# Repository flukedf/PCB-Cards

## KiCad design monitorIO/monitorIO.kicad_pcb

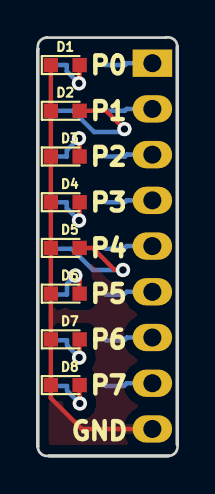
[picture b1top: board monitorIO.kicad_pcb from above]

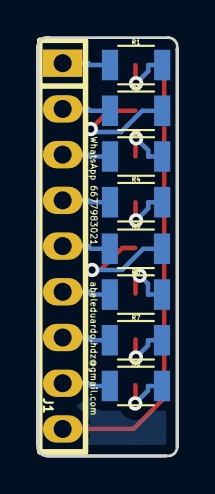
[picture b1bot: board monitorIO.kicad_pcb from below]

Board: 2 copper layers, 7.7 x 23.2 mm, 17 parts (9 on the bottom side), 17 nets.

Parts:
D1: P0; LED_0603
D2: P1; LED_0603
D3: P2; LED_0603
D4: P3; LED_0603
D5: P4; LED_0603
D6: P5; LED_0603
D7: P6; LED_0603
D8: P7; LED_0603
J1: Conn_01x09_Female; pin_strip_9
R1, R2, R3, R4, R5, R6, R7, R8: 220; R_1206

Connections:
GND: D1.1, D2.1, D3.1, D4.1, D5.1, D6.1, D7.1, D8.1, J1.9
unnamed: D1.2, R1.2
unnamed: D2.2, R2.2
unnamed: D3.2, R3.2
unnamed: D4.2, R4.2
unnamed: D5.2, R5.2
unnamed: D6.2, R6.2
unnamed: D7.2, R7.2
unnamed: D8.2, R8.2
unnamed: J1.1, R1.1
unnamed: J1.2, R2.1
unnamed: J1.3, R3.1
unnamed: J1.4, R4.1
unnamed: J1.5, R5.1
unnamed: J1.6, R6.1
unnamed: J1.7, R7.1
unnamed: J1.8, R8.1

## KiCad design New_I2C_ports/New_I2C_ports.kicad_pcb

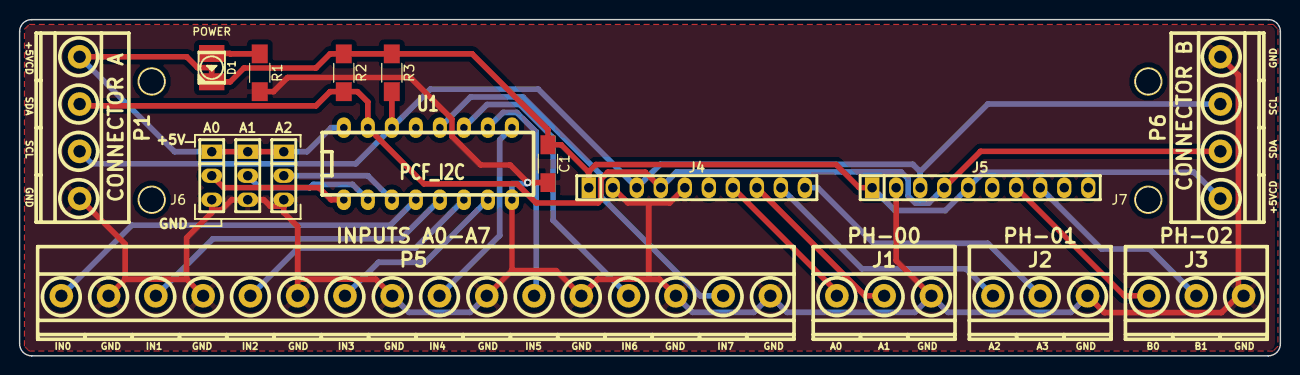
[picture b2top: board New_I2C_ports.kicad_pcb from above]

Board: 2 copper layers, 133.4 x 35.6 mm, 19 parts (0 on the bottom side), 22 nets.

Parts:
A0: A0; pin_strip_3
A1: A1; pin_strip_3
A2: A2; pin_strip_3
C1: 100nF; C_1206_HandSoldering
D1: POWER; Led_PLCC2_3528
J1: PH-00; mkds_1,5-3
J2: PH-01; mkds_1,5-3
J3: PH-02; mkds_1,5-3
J4: ADC-01; pin_strip_10
J5: ADC-02; pin_strip_10
J6: H1; Bracket_RielDin_2_hole
J7: H2; Bracket_RielDin_2_hole
P1: CONNECTOR A; mkds_1,5-4
P5: INPUTS A0-A7; mkds_1,5-16
P6: CONNECTOR B; mkds_1,5-4
R1: 330; R_1206_HandSoldering
R2, R3: 10K; R_1206_HandSoldering
U1: PCF_I2C; dil_16-300

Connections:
+5V: A0.1, A1.1, A2.1, C1.1, D1.2, J4.1, J5.1, J5.5, P1.1, P6.1, R2.1, R3.1, U1.16
A0: J1.1, J4.7
A1: J1.2, J4.8
A2: J2.1, J4.9
A3: J2.2, J4.10
B0: J3.1, J5.7
B1: J3.2, J5.8
GND: A0.3, A1.3, A2.3, C1.2, J1.3, J2.3, J3.3, J4.2, J4.5, J5.2, P1.4, P5.2, P5.4, P5.6, P5.8, P5.10, P5.12, P5.14, P5.16, P6.4, R1.2, U1.8
IN1: P5.1, U1.4
IN2: P5.3, U1.5
IN3: P5.5, U1.6
IN4: P5.7, U1.7
IN5: P5.9, U1.9
IN6: P5.11, U1.10
IN7: P5.13, U1.11
IN8: P5.15, U1.12
unnamed: D1.1, R1.1
unnamed: A0.2, U1.1
unnamed: A1.2, U1.2
unnamed: A2.2, U1.3
SCL: J4.3, J5.3, P1.3, P6.3, R3.2, U1.14
SDA: J4.4, J5.4, P1.2, P6.2, R2.2, U1.15

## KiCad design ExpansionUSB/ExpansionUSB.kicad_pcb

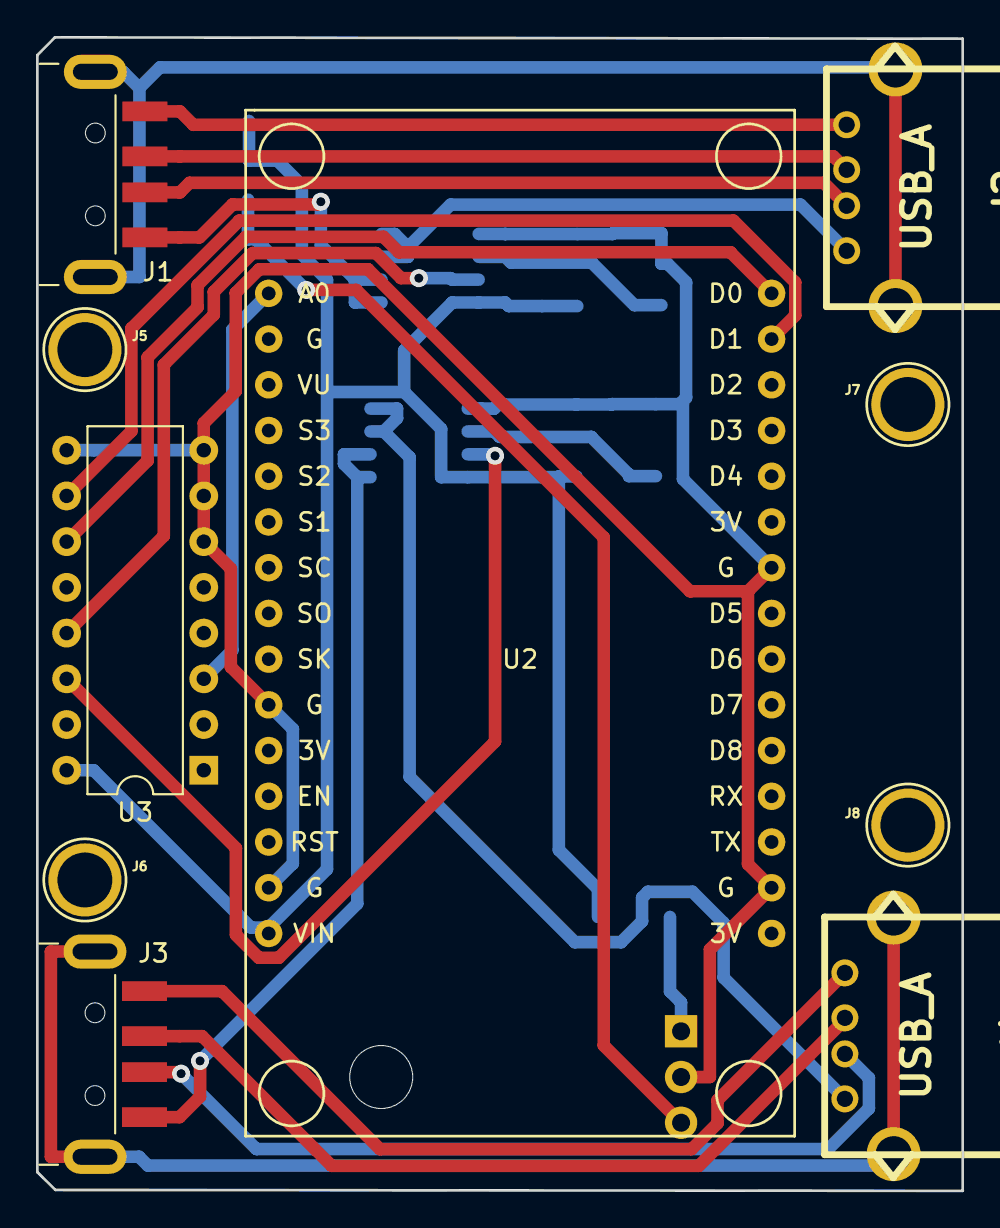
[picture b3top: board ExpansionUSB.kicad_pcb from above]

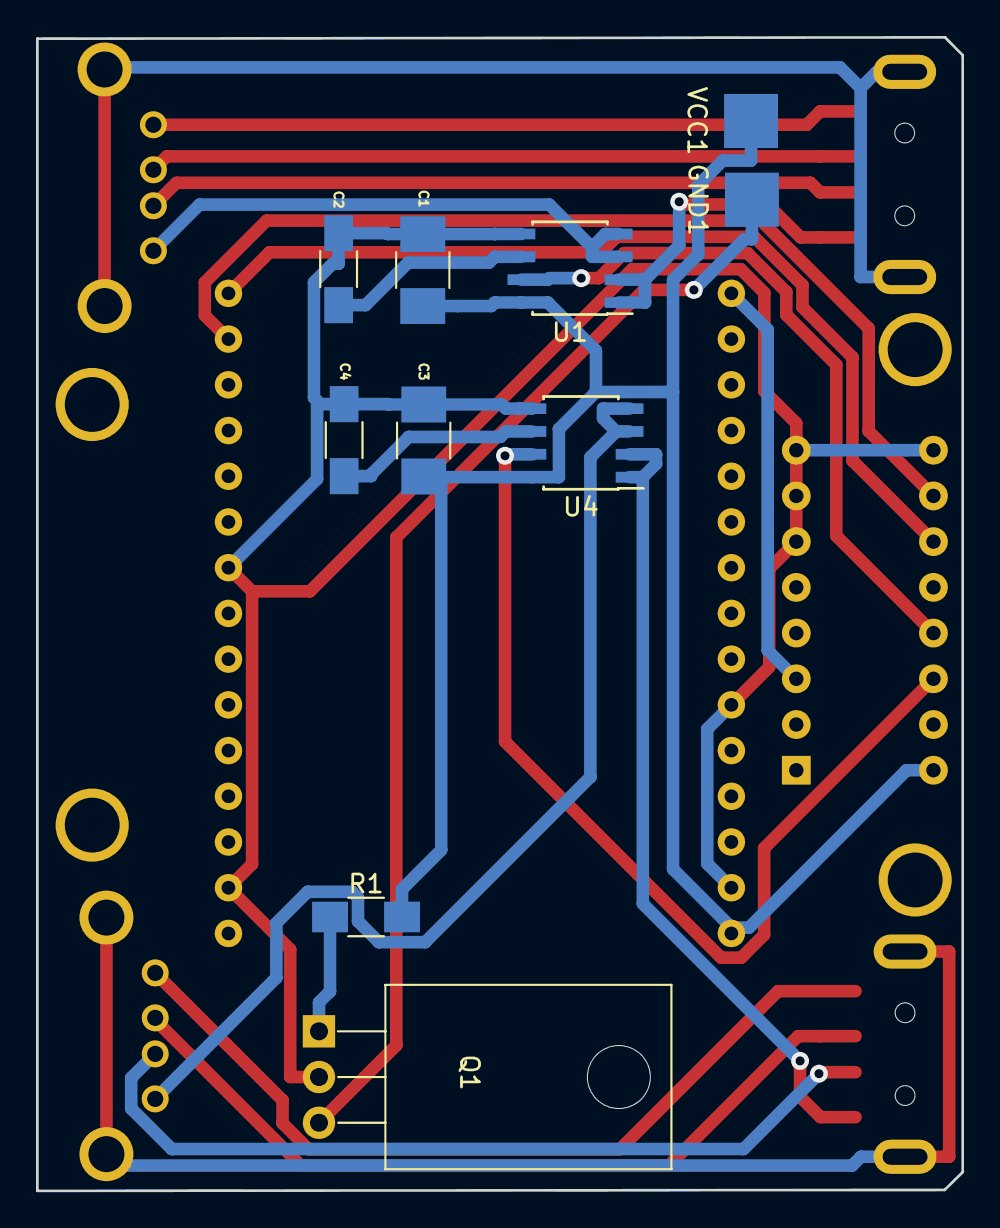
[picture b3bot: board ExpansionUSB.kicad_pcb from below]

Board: 2 copper layers, 51.4 x 64.1 mm, 20 parts (10 on the bottom side), 23 nets.

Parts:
C1, C3: 100nF; C_1210_HandSoldering
C2, C4: 1nF; C_1206_HandSoldering
GND1: HEART; Measurement_Point_Square-SMD-Pad_Big
J1, J3: USB_A; USB_A_CNCTech_1001-011-01101_Horizontal
J2, J4: USB_A; conn_usb_A
J5: H1; Arduino_1pin
J6: H2; Arduino_1pin
J7: H3; Arduino_1pin
J8: H4; Arduino_1pin
Q1: IRF640N; TO-220_Horizontal
R1: 10K; R_1206_HandSoldering
U1, U4: ACS712xLCTR-05B; SOIC-8_3.9x4.9mm_P1.27mm
U2: NodeMCU_1.0_(ESP-12E); NodeMCU-LoLinV3
U3: CD4051B; DIP-16_W7.62mm
VCC1: +5V; Measurement_Point_Square-SMD-Pad_Big

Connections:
+5V: C1.2, C3.2, R1.2, U1.8, U2.15, U3.16, U4.8, VCC1.1
GND: C1.1, C2.1, C3.1, C4.1, Q1.2, U1.5, U2.10, U2.14, U2.17, U2.24, U3.6, U3.7, U3.8, U3.9, U4.5
unnamed: C2.2, U1.6
unnamed: C4.2, U4.6
unnamed: GND1.1, Q1.3
unnamed: J1.1, U1.1, U1.2
unnamed: J1.2, J2.2
unnamed: J1.3, J2.3
unnamed: J1.4, J2.4
unnamed: J1.5, J2.5
unnamed: J2.1, U1.3, U1.4
unnamed: J3.1, U4.1, U4.2
unnamed: J3.2, J4.2
unnamed: J3.3, J4.3
unnamed: J3.4, J4.4
unnamed: J3.5, J4.5
unnamed: J4.1, U4.3, U4.4
unnamed: Q1.1, R1.1
unnamed: U1.7, U3.13
unnamed: U2.1, U3.3
unnamed: U2.29, U3.10
unnamed: U2.30, U3.11
unnamed: U3.14, U4.7

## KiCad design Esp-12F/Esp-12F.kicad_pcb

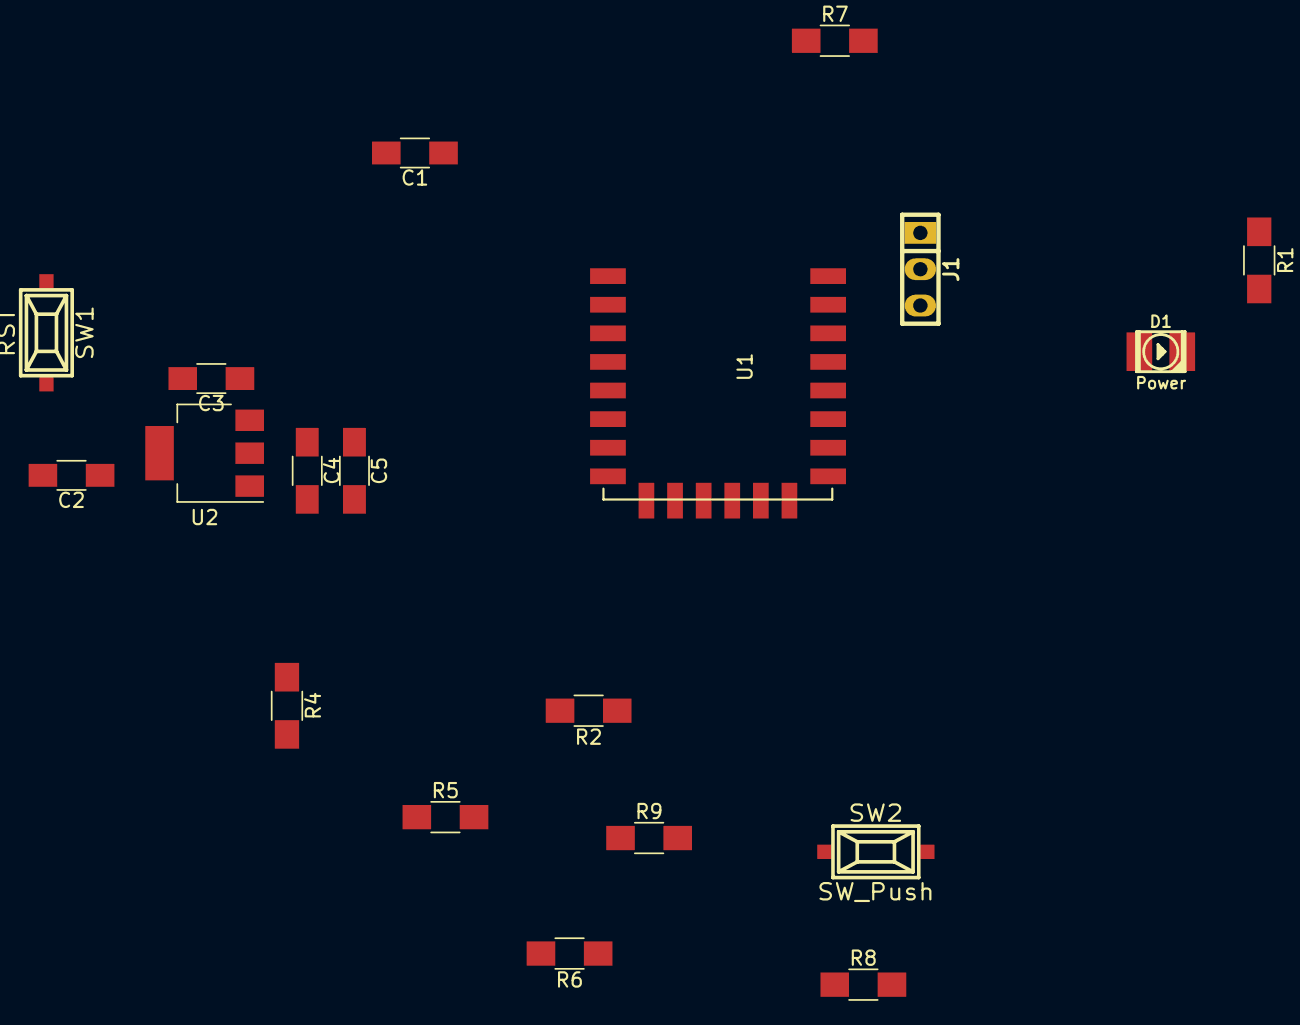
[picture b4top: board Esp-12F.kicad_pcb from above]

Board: 2 copper layers, 19 parts (0 on the bottom side), 13 nets, no tracks yet.

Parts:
C1, C5: 470pF; C_1206_HandSoldering
C2: 100uF; C_1206_HandSoldering
C3: 1uF; C_1206_HandSoldering
C4: 10uF; C_1206_HandSoldering
D1: Power; Led_PLCC2_3528
J1: UART; pin_strip_3
R1, R2, R9: 470; R_1206_HandSoldering
R4, R5, R7, R8: 12k; R_1206_HandSoldering
R6: 12K; R_1206_HandSoldering
SW1: RST; smd_push
SW2: SW_Push; smd_push
U1: ESP-12F; ESP-12E_SMD
U2: AMS1117-3.3; SOT-223-3Lead_TabPin2

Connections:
+3V3: C2.1, C4.1, C5.1, R1.1, R4.1, R5.1, R6.2, R7.2, U1.8, U2.2
+5V: C3.1, U2.3
GND: C1.2, C2.2, C3.2, C4.2, C5.2, J1.1, R8.2, SW1.2, SW2.2, U1.9, U2.1
unnamed: C1.1, R2.2, R4.2, SW1.1, U1.1
unnamed: D1.1, R2.1, U1.4
unnamed: D1.2, R1.2
unnamed: J1.2, U1.16
unnamed: J1.3, U1.15
unnamed: R5.2, U1.3
unnamed: R6.1, R9.1, U1.12
unnamed: R7.1, U1.11
unnamed: R8.1, U1.10
unnamed: R9.2, SW2.1

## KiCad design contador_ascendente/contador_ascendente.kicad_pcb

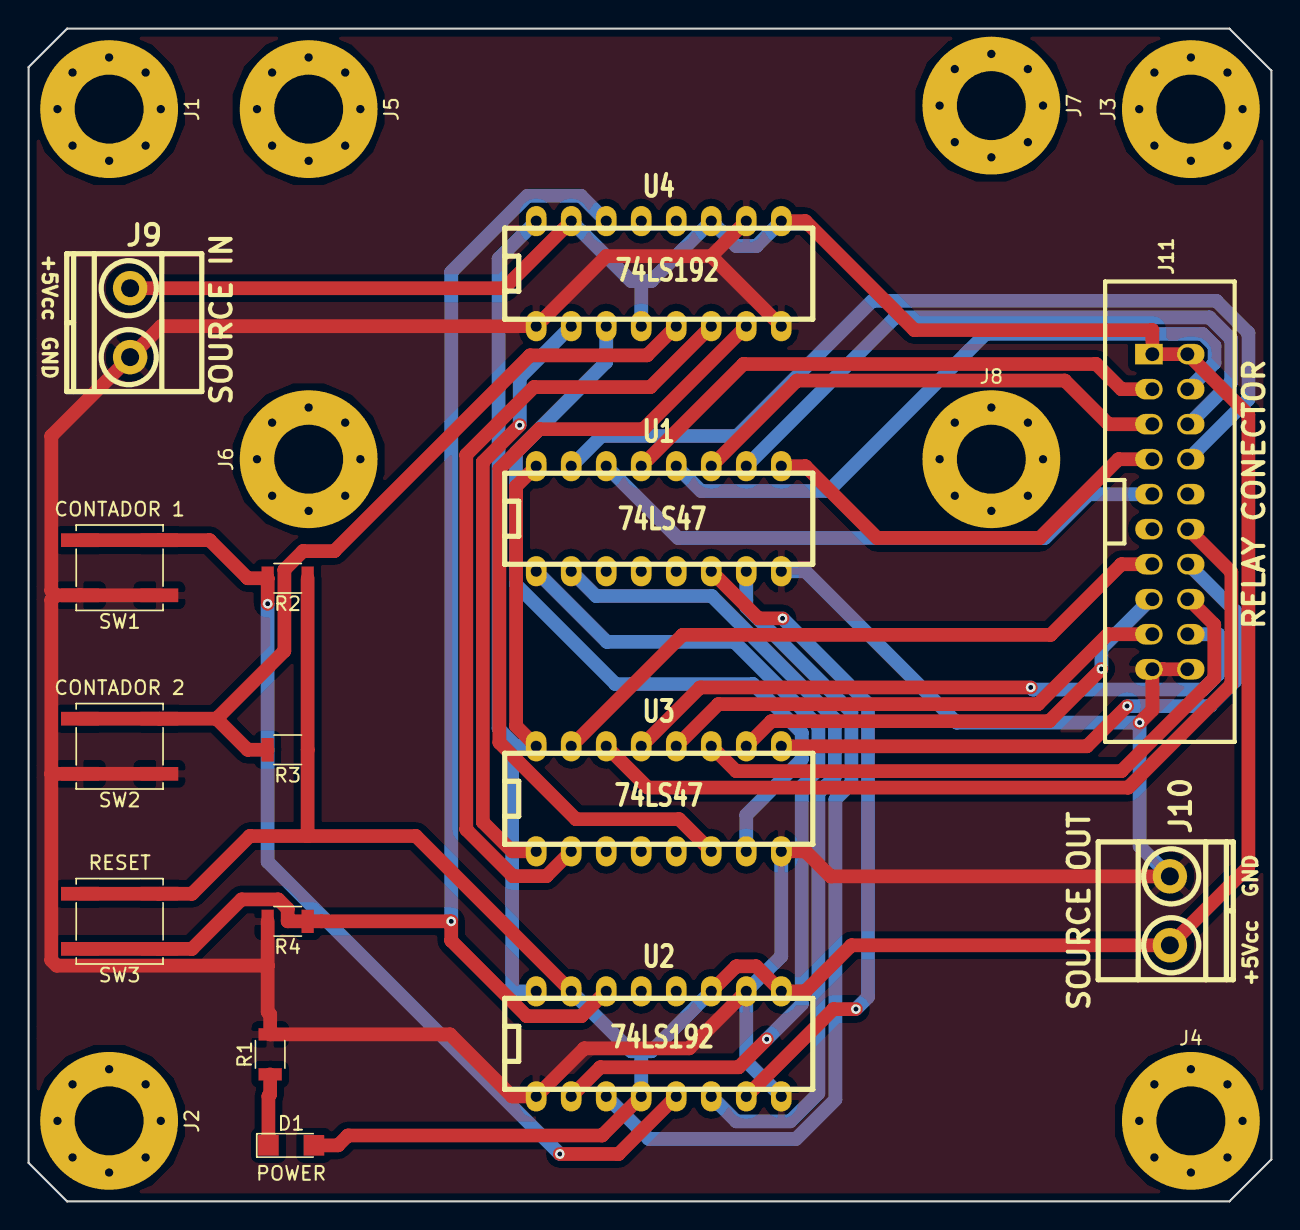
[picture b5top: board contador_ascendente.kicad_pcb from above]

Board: 2 copper layers, 90.2 x 85.1 mm, 23 parts (0 on the bottom side), 29 nets.

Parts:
D1: POWER; LED_1206
J1, J2: H1; MountingHole_5mm_Pad_Via
J3, J4: H2; MountingHole_5mm_Pad_Via
J5, J6: H3; MountingHole_5mm_Pad_Via
J7, J8: H4; MountingHole_5mm_Pad_Via
J9: SOURCE IN; mkds_1,5-2
J10: SOURCE OUT; mkds_1,5-2
J11: RELAY CONECTOR; vasch_strip_10x2
R1: 330; R_1206
R2, R3: 10K; R_1206
R4: 1K; R_1206
SW1: CONTADOR 1; SW_SPST_EVPBF
SW2: CONTADOR 2; SW_SPST_EVPBF
SW3: RESET; SW_SPST_EVPBF
U1, U3: 74LS47; dil_16-300
U2, U4: 74LS192; dil_16-300

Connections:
+5V: D1.2, J9.1, J10.1, J11.1, J11.2, R2.1, R3.1, SW3.2, U2.4, U2.9, U2.11, U2.15, U4.4, U4.9, U4.11, U4.15
/A1: J11.3, U1.13
/A2: J11.18, U3.13
/B1: J11.4, U1.12
/B2: J11.17, U3.12
/C1: J11.5, U1.11
/C2: J11.16, U3.11
/D1: J11.6, U1.10
/D2: J11.15, U3.10
/E1: J11.7, U1.9
/E2: J11.14, U3.9
/F1: J11.8, U1.15
/F2: J11.13, U3.15
/G1: J11.9, U1.14
/G2: J11.12, U3.14
GND: J9.2, J10.2, J11.19, J11.20, R1.2, R4.2, SW1.1, SW2.1, U1.8, U2.1, U2.8, U2.10, U3.8, U4.1, U4.8, U4.10
unnamed: D1.1, R1.1
unnamed: R2.2, SW1.2, U2.5
unnamed: R3.2, SW2.2, U4.5
unnamed: R4.1, SW3.1, U2.14, U4.14
unnamed: U1.1, U2.2
unnamed: U1.2, U2.6
unnamed: U1.6, U2.7
unnamed: U1.7, U2.3
unnamed: U3.1, U4.2
unnamed: U3.2, U4.6
unnamed: U3.6, U4.7
unnamed: U3.7, U4.3
VCC: U1.16, U2.16, U3.16, U4.16

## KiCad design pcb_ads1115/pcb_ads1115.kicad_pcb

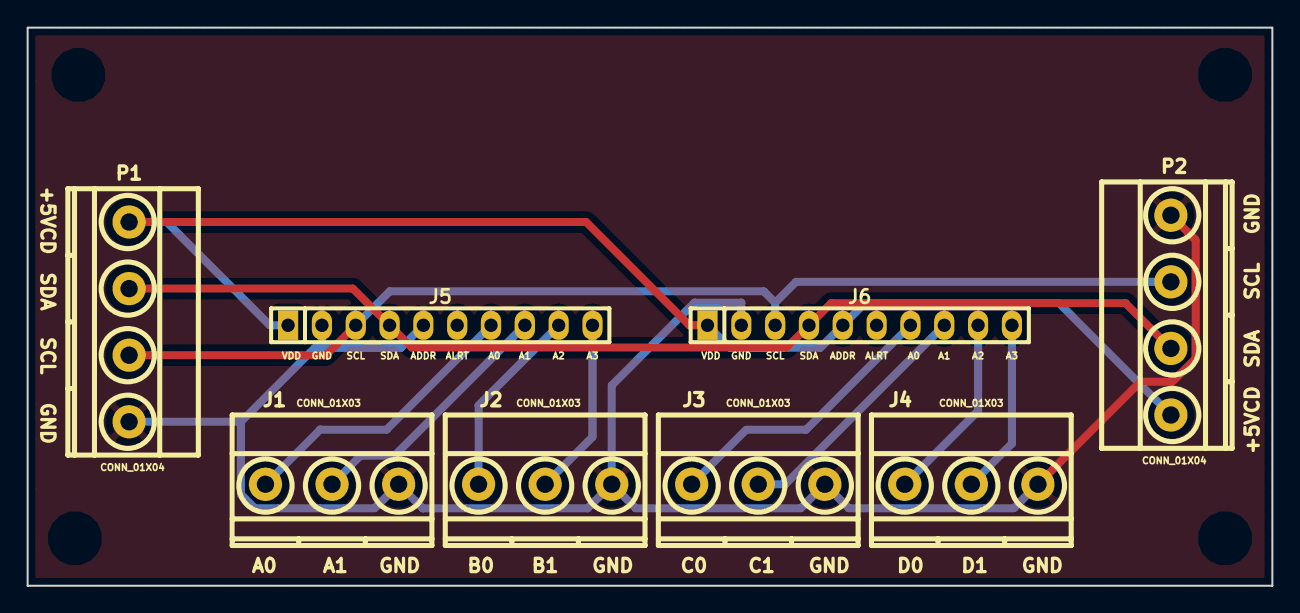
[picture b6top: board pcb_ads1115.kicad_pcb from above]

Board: 2 copper layers, 93.5 x 41.9 mm, 8 parts (0 on the bottom side), 12 nets.

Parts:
J1, J2, J3, J4: CONN_01X03; mkds_1,5-3
J5, J6: CONN_01X10; pin_strip_10
P1, P2: CONN_01X04; mkds_1,5-4

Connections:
+5V: J5.1, J6.1, J6.5, P1.1, P2.1
A0: J1.1, J5.7
A1: J1.2, J5.8
A2: J2.1, J5.9
A3: J2.2, J5.10
B0: J3.1, J6.7
B1: J3.2, J6.8
B2: J4.1, J6.9
B3: J4.2, J6.10
GND: J1.3, J2.3, J3.3, J4.3, J5.2, J5.5, J6.2, P1.4, P2.4
SCL: J5.3, J6.3, P1.3, P2.3
SDA: J5.4, J6.4, P1.2, P2.2

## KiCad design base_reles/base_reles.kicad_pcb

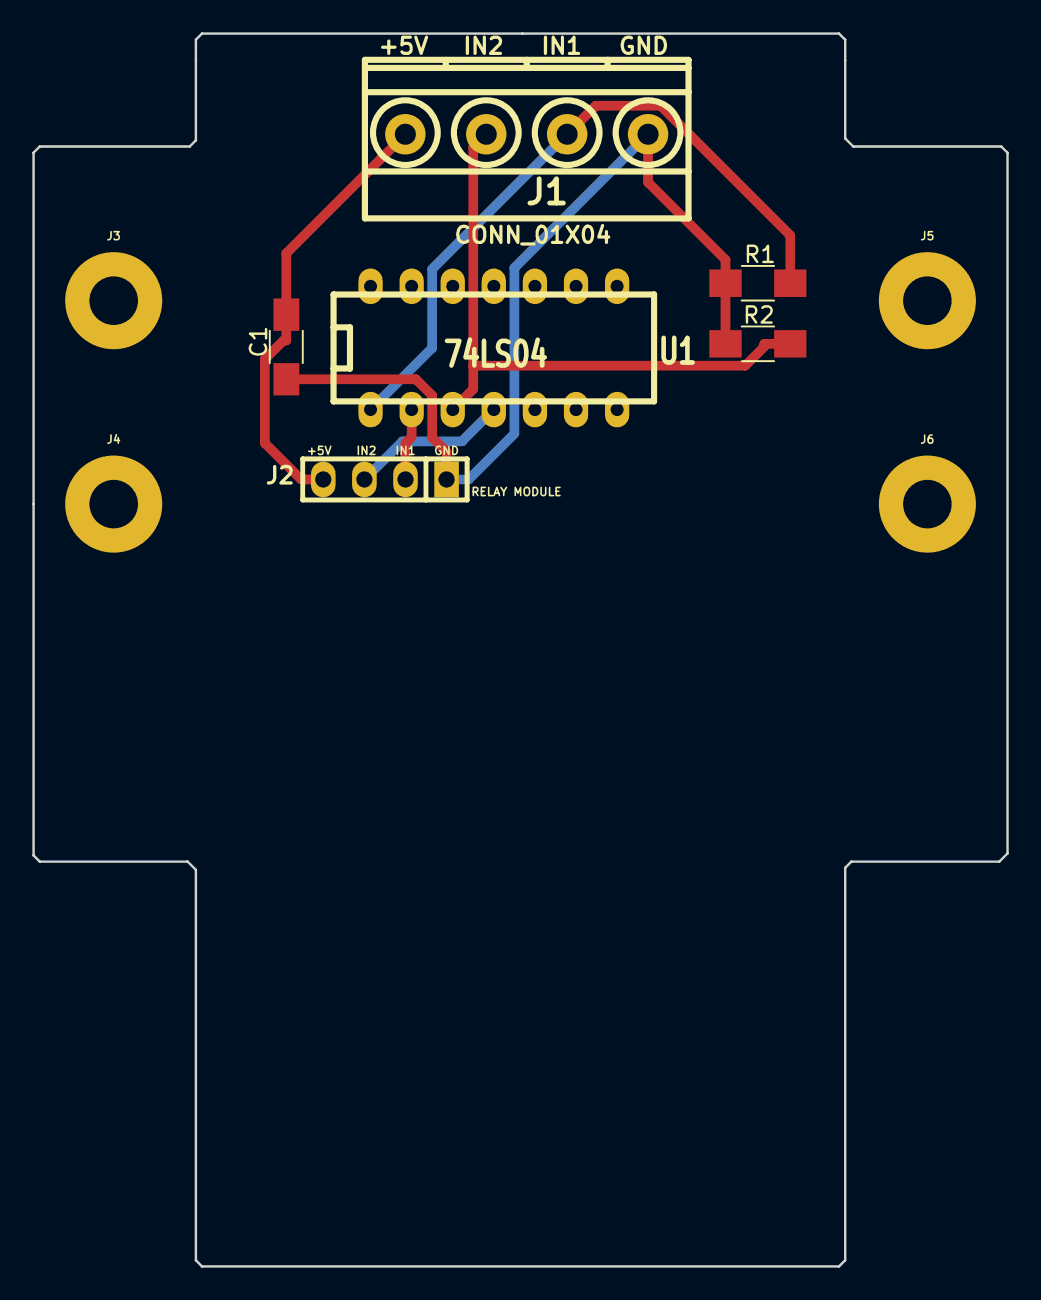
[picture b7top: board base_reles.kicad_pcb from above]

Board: 2 copper layers, 60.2 x 76.2 mm, 10 parts (0 on the bottom side), 6 nets.

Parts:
C1: .01uF; C_1206_HandSoldering
J1: CONN_01X04; mkds_1,5-4
J2: CONN_01X04; pin_socket_4
J3, J4, J5, J6: CONN_01X01; MountingHole_3mm_Pad
R1, R2: 1k; R_1206_HandSoldering
U1: 74LS04; dil_14-300

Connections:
+5V: C1.1, J1.4, J2.4
GND: C1.2, J1.1, J2.1, R1.2, R2.2
unnamed: J1.2, R1.1, U1.1
unnamed: J1.3, R2.1, U1.3
unnamed: J2.2, U1.2
unnamed: J2.3, U1.4

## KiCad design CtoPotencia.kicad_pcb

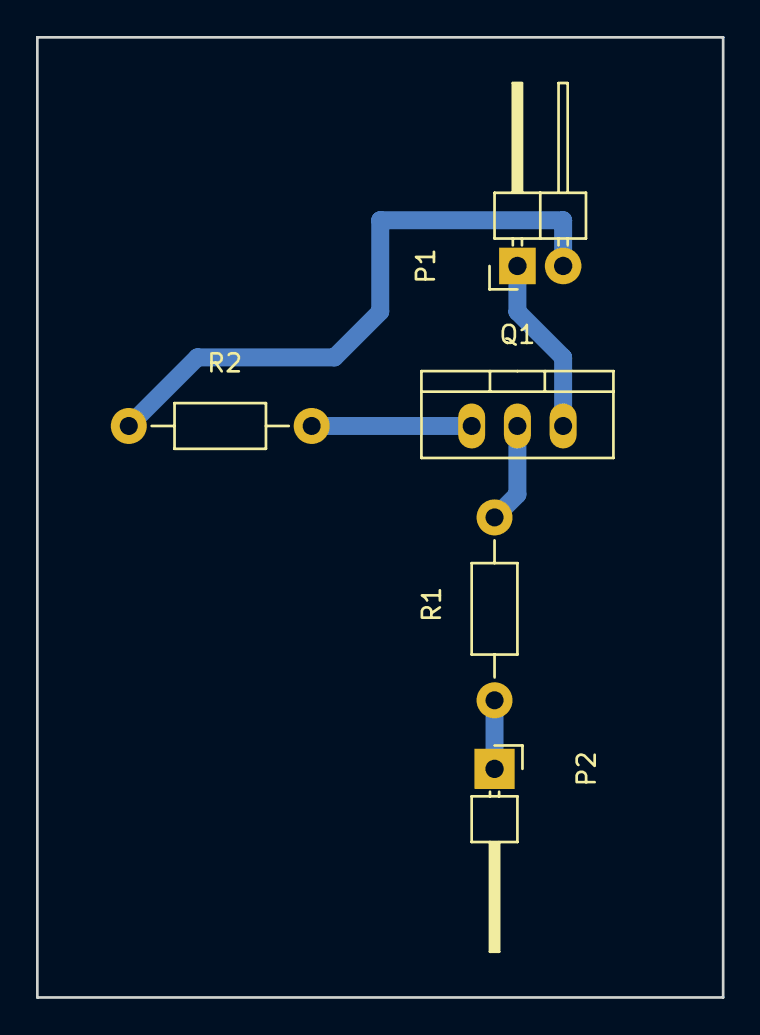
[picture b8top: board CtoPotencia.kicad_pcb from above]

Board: 2 copper layers, 38.1 x 53.3 mm, 5 parts (0 on the bottom side), 5 nets.

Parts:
P1: CONN_01X02; Pin_Header_Angled_1x02
P2: CONN_01X01; Pin_Header_Angled_1x01
Q1: Q_NMOS_DGS; TO-220_Neutral123_Vertical
R1, R2: R; Resistor_Horizontal_RM10mm

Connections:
+5V: P1.2, R2.1
GND: P1.1, Q1.3
unnamed: P2.1, R1.1
unnamed: Q1.1, R2.2
unnamed: Q1.2, R1.2

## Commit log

2018-11-03 PCB Design
2018-11-28 actualización expansion usb
2018-11-28 final usb expansion
2018-11-30 update ADC card
2018-12-05 Actualización tarjetas
2018-12-29 Expansion usb
2019-02-06 Update expansion
2019-04-17 new card
2019-07-31 new cards
2019-08-12 Monitor io
2019-10-14 changes in monitor led
